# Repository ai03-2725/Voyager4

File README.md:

# Voyager4
A tiny, fully featured 4-key macropad PCB

#### In light of recent claims that I am 100% liable for any of my open source PCBs, I am adding this disclaimer.
#### I provide these PCBs as a reference for designing keyboard PCBs. Using them within your projects will require a will to do research of one's own and to learn the workings of them, potentially fixing issues if they exist.
# I provide these PCBs without liability and without any guarantees regarding functionality, as expressed in the MIT license under which all of these PCBs are licensed.

### Features
* In-switch LED backlighting
* RGB underglow
* Over-current and static discharge protection
* Fully open-source
* Absolutely tiny

### The Voyager PCB Family
The Voyager PCBs offer fully featured PCBs fit for any keyboard, whether mass production or high-end.

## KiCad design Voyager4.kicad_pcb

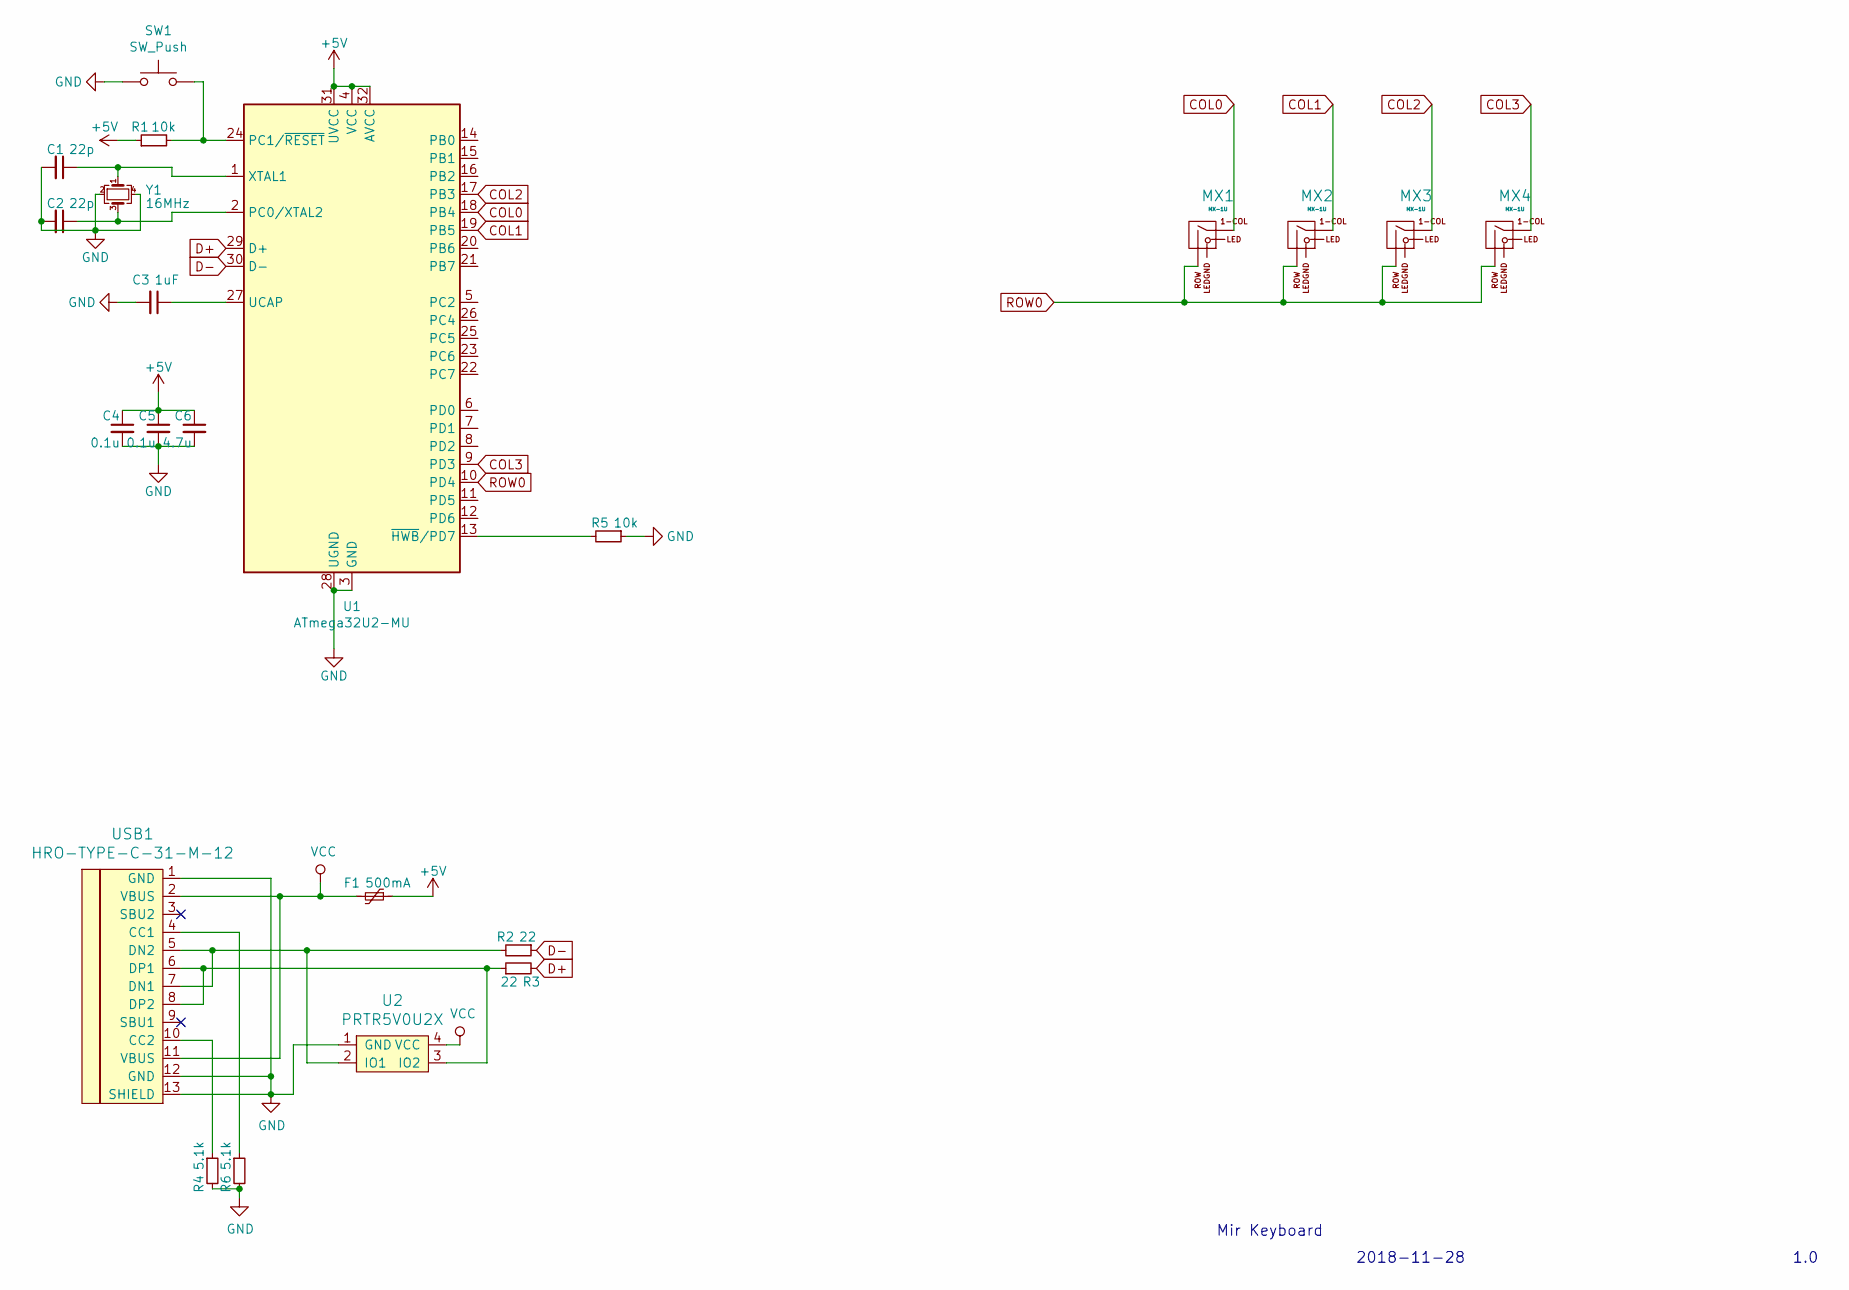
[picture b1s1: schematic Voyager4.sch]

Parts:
C1, C2: 22p; C_0603_1608Metric
C3: 1uF; C_0603_1608Metric
C4, C5: 0.1u; C_0603_1608Metric
C6: 4.7u; C_0603_1608Metric
F1: 500mA; Fuse_1206_3216Metric
MX1, MX2, MX3, MX4: MX-1U; MXOnly-1U-Hotswap
R1, R5: 10k; R_0603_1608Metric
R2, R3: 22; R_0603_1608Metric
R4, R6: 5.1k; R_0603_1608Metric
SW1: SW_Push; Alps-SKSV-LargerPads
U1: ATmega32U2-MU; QFN-32-1EP_5x5mm_Pitch0.5mm
U2: PRTR5V0U2X; SOT143B
USB1: HRO-TYPE-C-31-M-12; HRO-TYPE-C-31-M-12-Assembly
Y1: 16MHz; Crystal_SMD_3225-4pin_3.2x2.5mm

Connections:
+5V: C4.1, C5.1, C6.1, F1.1, R1.1, U1.4 (VCC), U1.31 (UVCC), U1.32 (AVCC)
COL0: MX1.1 (COL), U1.18 (PB4)
COL1: MX2.1 (COL), U1.19 (PB5)
COL2: MX3.1 (COL), U1.17 (PB3)
COL3: MX4.1 (COL), U1.9 (PD3)
D+: R3.2, U1.29 (D+)
D-: R2.1, U1.30 (D-)
GND: C1.2, C2.2, C3.2, C4.2, C5.2, C6.2, R4.2, R5.1, R6.2, SW1.1, U1.3 (GND), U1.28 (UGND), U1.33 (GND), U2.1 (GND), USB1.1 (GND), USB1.12 (GND), USB1.13 (SHIELD), Y1.2, Y1.4; also elsewhere on the board
unnamed: C1.1, U1.1 (XTAL1), Y1.1
unnamed: C2.1, U1.2 (PC0/XTAL2), Y1.3
unnamed: C3.1, U1.27 (UCAP)
unnamed: R1.2, SW1.2, U1.24 (PC1/~RESET)
unnamed: R2.2, U2.2 (IO1), USB1.5 (DN2), USB1.7 (DN1)
unnamed: R3.1, U2.3 (IO2), USB1.6 (DP1), USB1.8 (DP2)
unnamed: R4.1, USB1.10 (CC2)
unnamed: R5.2, U1.13 (~HWB~/PD7)
unnamed: R6.1, USB1.4 (CC1)
ROW0: MX1.2 (ROW), MX2.2 (ROW), MX3.2 (ROW), MX4.2 (ROW), U1.10 (PD4)
VCC: F1.2, U2.4 (VCC), USB1.2 (VBUS), USB1.11 (VBUS)

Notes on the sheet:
Mir Keyboard
2018-11-28
1.0

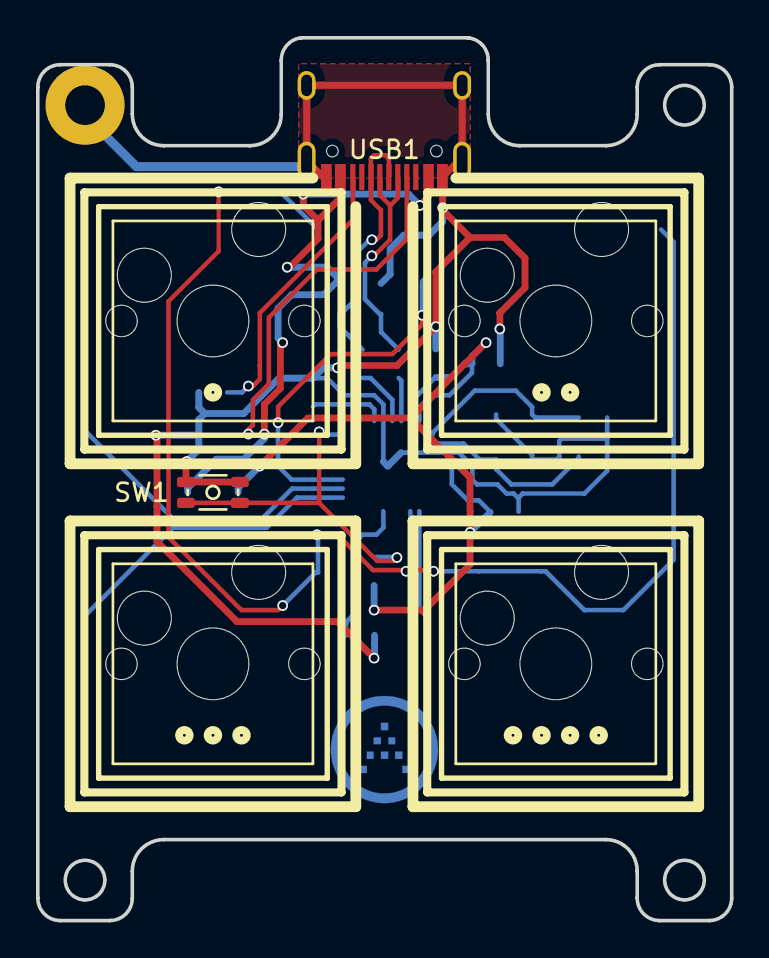
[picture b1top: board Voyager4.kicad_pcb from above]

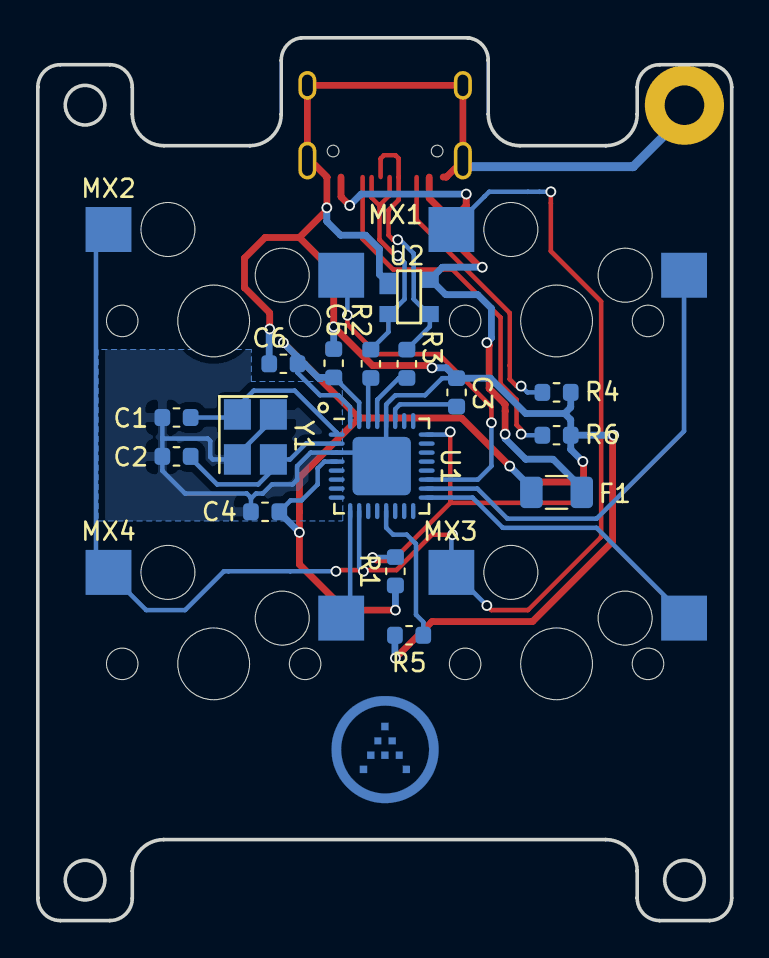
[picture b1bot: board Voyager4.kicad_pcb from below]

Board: 2 copper layers, 38.5 x 49.0 mm, 23 parts (16 on the bottom side), 19 nets.

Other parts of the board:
GroundingPad: MountingHole_2.2mm_M2_Pad

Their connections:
GND: GroundingPad.1; also elsewhere on the board

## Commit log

2019-01-27 Add submodules
2019-01-27 Build the PCB
2019-02-17 Prepare for redo
2019-02-18 Progress
2019-05-31 Repair project, rev 2.0
2019-05-31 Save progress
2019-08-09 Finish new PCB
